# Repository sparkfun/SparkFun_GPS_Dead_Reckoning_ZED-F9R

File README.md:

SparkFun GPS-RTK Dead Reckoning Breakout - ZED-F9R, u.FL and SMA (Qwiic)
========================================

<table class="table table-hover table-striped table-bordered">
  <tr align="center">
   <td></td>
   <td></td>
  </tr>
  <tr align="center">
   <td><i>SparkFun GPS-RTK Dead Reckoning Breakout <br /> - ZED-F9R, u.FL (Qwiic) [<a href="https://www.sparkfun.com/products/22693">22693</a>]</i></td>
   <td><i>SparkFun GPS-RTK Dead Reckoning Breakout <br /> - ZED-F9R, SMA (Qwiic) [<a href="https://www.sparkfun.com/products/22660">GPS-22660</a>]</i></td>
  </tr>
</table>

The SparkFun GPS-RTK Dead Reckoning ZED-F9R Breakout (u.FL and SMA) is a high precision, sensor fusion GPS board with equally impressive configuration options and takes advantage of u-blox's Automotive Dead Reckoning (ADR) technology. The ZED-F9R module provides a highly accurate and continuous position by fusing a 3D IMU sensor, wheel ticks, a vehicle dynamics model, correction data, and GNSS measurements.

The ZED-F9R module is a 184-channel u-blox F9 engine GNSS receiver, meaning it can receive signals from the GPS, GLONASS, Galileo, and BeiDou constellations with ~0.2 meter accuracy! That's right, such accuracy can be achieved with an RTK navigation solution when used with a correction source. Note that the ZED-F9R can only operate as a rover, so you will need to connect to a base station. The module supports concurrent reception of four GNSS systems. The combination of GNSS and integrated 3D sensor measurements on the ZED-F9R provide accurate, real-time positioning rates of up to 30Hz.

Compared to other GPS modules, this breakout maximizes position accuracy in dense cities or covered areas. Even under poor signal conditions, continuous positioning is provided in urban environments and is also available during complete signal loss (e.g. short tunnels and parking garages). The ZED-F9R is the ultimate solution for autonomous robotic applications that require accurate positioning under challenging conditions.

Additionally, this u-blox receiver supports I2C (u-blox calls this Display Data Channel) which makes it perfect for the Qwiic compatibility so we don't have to use up our precious UART ports. Utilizing our handy Qwiic system, no soldering is required to connect it to the rest of your system. However, we still have broken out 0.1"-spaced pins in case you prefer to use a breadboard.

U-blox based GPS products are configurable using the popular, but dense, windows program called u-center. Plenty of different functions can be configured on the ZED-F9R: baud rates, update rates, geofencing, spoofing detection, external interrupts, SBAS/D-GPS, etc. All of this can be done within the SparkFun Arduino Library!

The SparkFun ZED-F9R GPS Breakout is also equipped with an on-board rechargeable battery that provides power to the RTC on the ZED-F9R. This reduces the time-to-first fix from a cold start (~24s) to a hot start (~2s). The battery will maintain RTC and GNSS orbit data without being connected to power for plenty of time.

Repository Contents
-------------------

* **/Documentation** - Data sheets, additional product information
* **/Hardware** - Eagle design files (.brd, .sch)
* **/Production** - Production panel files (.brd)

Documentation
--------------
* **[Library](https://github.com/sparkfun/SparkFun_u-blox_GNSS_v3)** - Arduino library v3 for the ZED-F9R.
    * _**Note**: We support two versions of the SparkFun u-blox GNSS library. [Version 2](https://github.com/sparkfun/SparkFun_u-blox_GNSS_Arduino_Library) and [Version 3](https://github.com/sparkfun/SparkFun_u-blox_GNSS_v3). Version 3 uses the u-blox Configuration Interface (VALSET and VALGET) to configure the module, instead of the deprecated UBX-CFG messages. For modules like the F9 and M10, we recommend upgrading to Version 3. However, older modules like the M8 do not support the Configuration Interface. For those you will need to keep using Version 2 of the library. We will continue to support both._
* **[Hookup Guide](https://learn.sparkfun.com/tutorials/1172)** - Basic hookup guide for the ZED-F9R.

Product Versions
----------------
* [GPS-22693](https://www.sparkfun.com/products/22693) - u.FL, v1.2
* [GPS-22660](https://www.sparkfun.com/products/22660) - SMA, V1.1
* [GPS-16344](https://www.sparkfun.com/products/16344) - u.FL, v1.0 initial release

Version History
---------------
* [v1.0](https://github.com/sparkfun/SparkFun_GPS_Dead_Reckoning_ZED-F9R/releases/tag/v1.0) - Initial Release

License Information
-------------------

This product is _**open source**_! 

Please review the LICENSE.md file for license information. 

If you have any questions or concerns on licensing, please contact technical support on our [SparkFun forums](https://forum.sparkfun.com/viewforum.php?f=152).

Distributed as-is; no warranty is given.

- Your friends at SparkFun.

_<COLLABORATION CREDIT>_

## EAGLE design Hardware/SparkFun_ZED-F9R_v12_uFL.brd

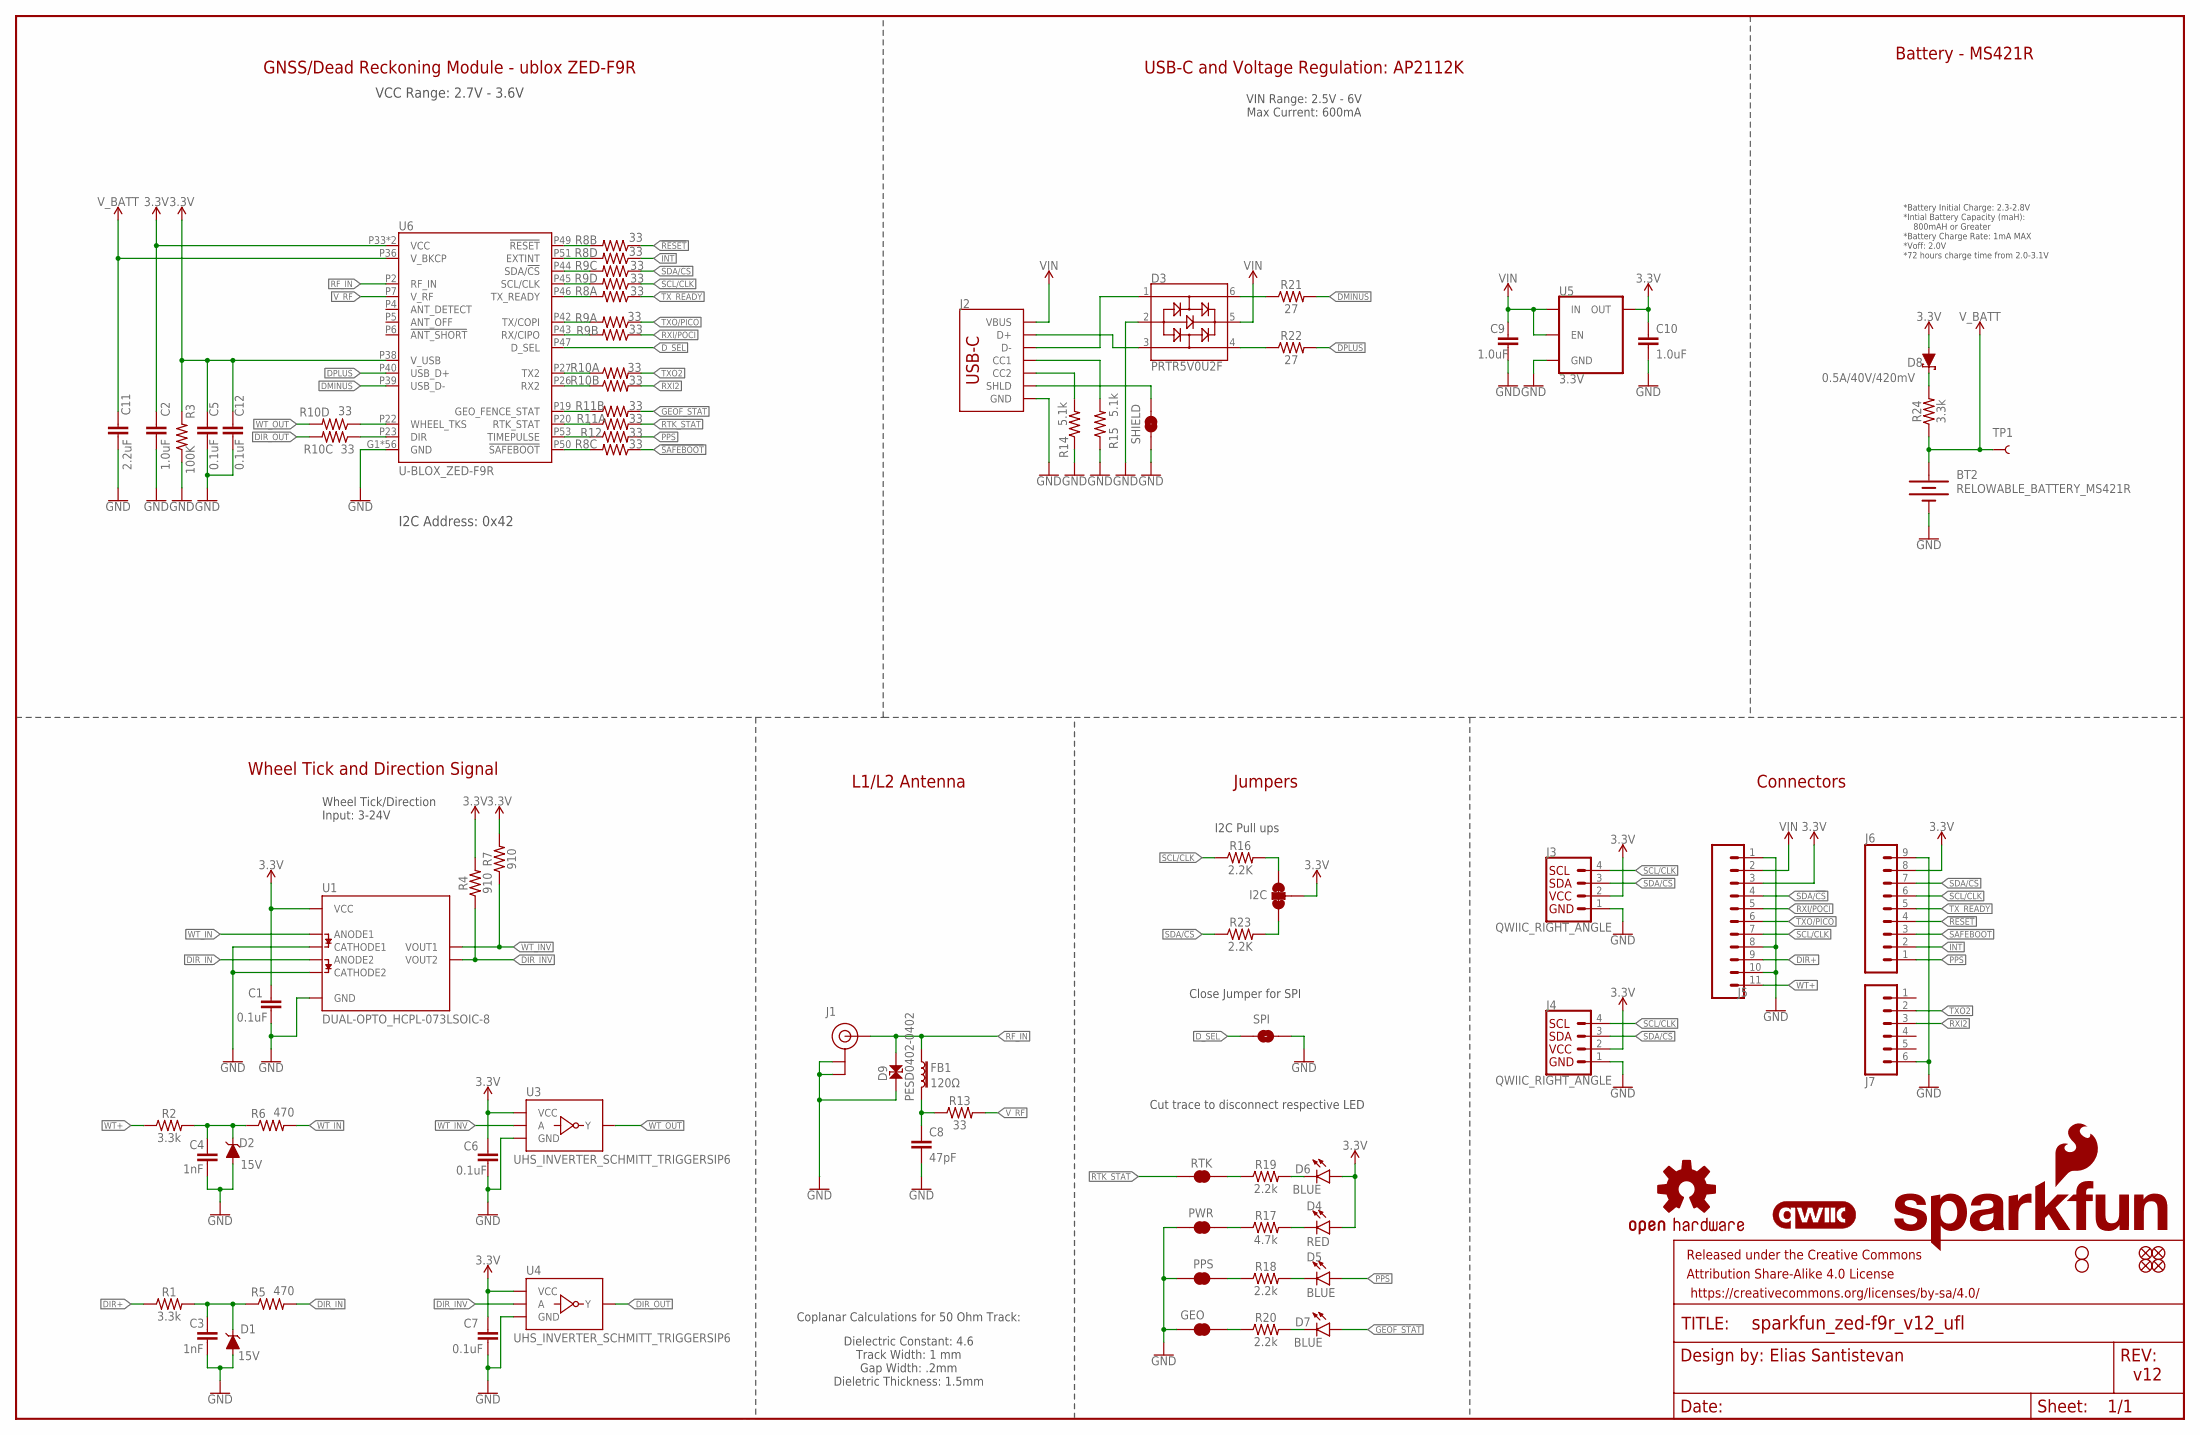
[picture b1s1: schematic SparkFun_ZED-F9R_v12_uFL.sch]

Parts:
$1_25_$_2020-03-30_22-52-05: STAND-OFFTIGHT; STAND-OFF-TIGHT
BT2: RELOWABLE_BATTERY_MS421R; MS421R_IV03E
C1, C5, C6, C7, C12: 0.1uF; 0402-TIGHT
C2, C9, C10: 1.0uF; 0402-TIGHT
C3, C4: 1nF; 0402
C8: 47pF; 0402
C11: 2.2uF; 0402-TIGHT
D1, D2: 15V; SOT23-3
D3: PRTR5V0U2F; SOT886
D4: RED; LED-0603
D5, D6, D7: BLUE; LED-0603
D8: 0.5A/40V/420mV; SOD-323
D9: PESD0402-0402; 0402
FB1: 120Ω; 0402
FD1, FD2, FD3, FD4: FIDUCIALUFIDUCIAL; FIDUCIAL-MICRO
FRAME1: FRAME-LEDGER; CREATIVE_COMMONS
GEO: JUMPER-SMT_2_NC_TRACE_SILK; SMT-JUMPER_2_NC_TRACE_SILK
H2: STAND-OFFTIGHT; STAND-OFF-TIGHT
I2C: JUMPER-SMT_3_2-NC_TRACE_SILK; SMT-JUMPER_3_2-NC_TRACE_SILK
J1: U.FL
J2: USB_C_2-LAYER_PADS; USB-C-16P-2LAYER-PADS
J3, J4: QWIIC_RIGHT_ANGLE; JST04_1MM_RA
J5: CONN_111X11_NO_SILK; 1X11_NO_SILK
J6: CONN_09NO_SILK; 1X09_NO_SILK
J7: CONN_06NO_SILK_NO_POP; 1X06_NO_SILK
LOGO1: OSHW-LOGOS; OSHW-LOGO-S
LOGO2: QWIIC_LOGO_4MM; QWIIC_4MM
LOGO3: SFE_LOGO_NAME_FLAME.2_INCH; SFE_LOGO_NAME_FLAME_.2
PPS: JUMPER-SMT_2_NC_TRACE_SILK; SMT-JUMPER_2_NC_TRACE_SILK
PWR: JUMPER-SMT_2_NC_TRACE_SILK; SMT-JUMPER_2_NC_TRACE_SILK
R1, R2, R24: 3.3k; 0603
R3: 100K; 0402
R4, R7: 910; 0603
R5, R6: 470; 0603
R8, R9, R10, R11: 33; 1206_RA
R12, R13: 33; 0603
R14, R15: 5.1k; 0402
R16, R23: 2.2K; 0402
R17: 4.7k; 0603
R18, R19, R20: 2.2k; 0603
R21, R22: 27; 0603
RTK: JUMPER-SMT_2_NC_TRACE_SILK; SMT-JUMPER_2_NC_TRACE_SILK
SHIELD: JUMPER-SMT_2_NC_TRACE_SILK; SMT-JUMPER_2_NC_TRACE_SILK
SPI: JUMPER-SMT_2_NO_SILK; SMT-JUMPER_2_NO_SILK
TP1: TEST-POINT3X5; PAD.03X.05
U1: DUAL-OPTO_HCPL-073LSOIC-8; SO08
U3, U4: UHS_INVERTER_SCHMITT_TRIGGERSIP6; SIP6_MICROPAK2
U5: 3.3V; SOT23-5
U6: U-BLOX_ZED-F9R; UBLOX_ZED_F9R

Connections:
3.3V: C1.1, C2.1, C5.1, C6.1, C7.1, C10.1, C12.1, D4.A, D6.A, D8.A, I2C.2, J3.2, J4.2, J5.3, J6.8, R3.2, R4.2, R7.2, U1.8 (VCC), U3.P6 (VCC), U4.P6 (VCC), U5.5 (OUT), U6.P33 (VCC), U6.P34 (VCC), U6.P38 (V_USB)
!RESET: J6.4, R8.P2 (1)
!SAFEBOOT: J6.3, R8.P3 (1)
DIR+: J5.9, R1.1
DIR_IN: R5.2, U1.4 (ANODE2)
DIR_INV: R4.1, U1.6 (VOUT2), U4.P2 (A)
DIR_OUT: R10.P6 (2), U4.P4 (Y)
DMINUS: R21.2, U6.P39 (USB_D-)
DPLUS: R22.2, U6.P40 (USB_D+)
D_SEL: SPI.1, U6.P47 (D_SEL)
GEOF_STAT: D7.A, R11.P7 (2)
GND: BT2.-, C1.2, C2.2, C3.2, C4.2, C5.2, C6.2, C7.2, C8.2, C9.2, C10.2, C11.2, C12.2, D1.1 (A), D2.1 (A), D3.2, D9.1, GEO.1, J1.1 (GND), J1.2 (GND), J2.GND, J2.GND2 (GND), J3.1, J4.1, J5.1, J5.8, J5.10, J6.9, J7.6, PPS.1, PWR.1, R3.1, R14.1, R15.1, SHIELD.1, SPI.2, U1.2 (CATHODE1), U1.3 (CATHODE2), U1.5 (GND), U3.P3 (GND), U4.P3 (GND), U5.2 (GND), U6.G1 (GND), U6.G2 (GND), U6.G3 (GND), U6.G4 (GND), U6.G5 (GND), U6.G6 (GND), U6.G7 (GND), U6.G8 (GND), U6.G9 (GND), U6.G10 (GND), U6.G11 (GND), U6.G12 (GND), U6.G13 (GND), U6.G14 (GND), U6.G15 (GND), U6.G16 (GND), U6.G17 (GND), U6.G18 (GND), U6.G19 (GND), U6.G20 (GND), U6.G21 (GND), U6.G22 (GND), U6.G23 (GND), U6.G24 (GND), U6.G25 (GND), U6.G26 (GND), U6.G27 (GND), U6.G28 (GND), U6.G29 (GND), U6.G30 (GND), U6.G31 (GND), U6.G32 (GND), U6.G33 (GND), U6.G34 (GND), U6.G35 (GND), U6.G36 (GND), U6.G37 (GND), U6.G38 (GND), U6.G39 (GND), U6.G40 (GND), U6.G41 (GND), U6.G42 (GND), U6.G43 (GND), U6.G44 (GND), U6.G45 (GND), U6.G46 (GND), U6.G47 (GND), U6.G48 (GND), U6.P1 (GND), U6.P3 (GND), U6.P12 (GND), U6.P14 (GND), U6.P32 (GND), U6.P37 (GND), U6.P41 (GND), U6.P48 (GND)
INT: J6.2, R8.P4 (1)
unnamed: I2C.1, R23.2
unnamed: D8.C, R24.2
unnamed: I2C.3, R16.2
unnamed: D4.C, R17.2
unnamed: C8.1, FB1.2, R13.1
unnamed: D3.3, J2.A6 (D+), J2.B6 (D+)
unnamed: D3.1, J2.A7 (D-), J2.B7 (D-)
unnamed: PWR.2, R17.1
unnamed: D3.6, R21.1
unnamed: D3.4, R22.1
unnamed: R8.P7 (2), U6.P49 (!RESET!)
unnamed: R8.P5 (2), U6.P51 (EXTINT)
unnamed: J2.B5 (CC2), R14.2
unnamed: J2.A5 (CC1), R15.2
unnamed: R9.P6 (2), U6.P44 (SDA/!CS!)
unnamed: R9.P5 (2), U6.P45 (SCL/CLK)
unnamed: R8.P8 (2), U6.P46 (TX_READY)
unnamed: R9.P8 (2), U6.P42 (TX/COPI)
unnamed: R9.P7 (2), U6.P43 (RX/CIPO)
unnamed: R10.P1 (1), U6.P27 (TX2)
unnamed: R19.1, RTK.2
unnamed: PPS.2, R18.1
unnamed: D5.C, R18.2
unnamed: D6.C, R19.2
unnamed: R10.P2 (1), U6.P26 (RX2)
unnamed: R11.P2 (1), U6.P19 (GEO_FENCE_STAT)
unnamed: R11.P1 (1), U6.P20 (RTK_STAT)
unnamed: R12.1, U6.P53 (TIMEPULSE)
unnamed: R8.P6 (2), U6.P50 (!SAFEBOOT!)
unnamed: R10.P4 (1), U6.P22 (WHEEL_TKS)
unnamed: R10.P3 (1), U6.P23 (DIR)
unnamed: GEO.2, R20.1
unnamed: D7.C, R20.2
unnamed: C4.1, D2.3 (C), R2.2, R6.1
unnamed: C3.1, D1.3 (C), R1.2, R5.1
PPS: D5.A, J6.1, R12.2
RF_IN: D9.2, FB1.1, J1.FEED (SIGNAL), U6.P2 (RF_IN)
RTK_STAT: R11.P8 (2), RTK.1
RXI2: J7.3, R10.P7 (2)
RXI/POCI: J5.5, R9.P2 (1)
SCL/CLK: J3.4, J4.4, J5.7, J6.6, R9.P4 (1), R16.1
SDA/!CS: J3.3, J4.3, J5.4, J6.7, R9.P3 (1), R23.1
SHIELD: J2.SHLD1 (SHLD), J2.SHLD2 (SHLD), J2.SHLD3 (SHLD), J2.SHLD4 (SHLD), SHIELD.2
TXO2: J7.2, R10.P8 (2)
TXO/PICO: J5.6, R9.P1 (1)
TX_READY: J6.5, R8.P1 (1)
VIN: C9.1, D3.5, J2.VBUS1 (VBUS), J2.VBUS2 (VBUS), J5.2, U5.1 (IN), U5.3 (EN)
V_BATT: BT2.+, C11.1, R24.1, TP1.1, U6.P36 (V_BKCP)
V_RF: R13.2, U6.P7 (V_RF)
WT+: J5.11, R2.1
WT_IN: R6.2, U1.1 (ANODE1)
WT_INV: R7.1, U1.7 (VOUT1), U3.P2 (A)
WT_OUT: R10.P5 (2), U3.P4 (Y)

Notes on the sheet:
v12
Elias Santistevan
GNSS/Dead Reckoning Module - ublox ZED-F9R
Battery - MS421R
Connectors
Jumpers
Close Jumper for SPI
I2C Pull ups
Cut trace to disconnect respective LED
L1/L2 Antenna
*Battery Initial Charge: 2.3-2.8V *Intial Battery Capacity (maH): 800mAH or Greater *Battery Charge Rate: 1mA MAX *Voff: 2.0V *72 hours charge time from 2.0-3.1V
VIN Range: 2.5V - 6V Max Current: 600mA
USB-C and Voltage Regulation: AP2112K
VCC Range: 2.7V - 3.6V
I2C Address: 0x42
Wheel Tick and Direction Signal
Wheel Tick/Direction Input: 3-24V
Coplanar Calculations for 50 Ohm Track:
Dielectric Constant: 4.6 Track Width: 1 mm Gap Width: .2mm Dieletric Thickness: 1.5mm

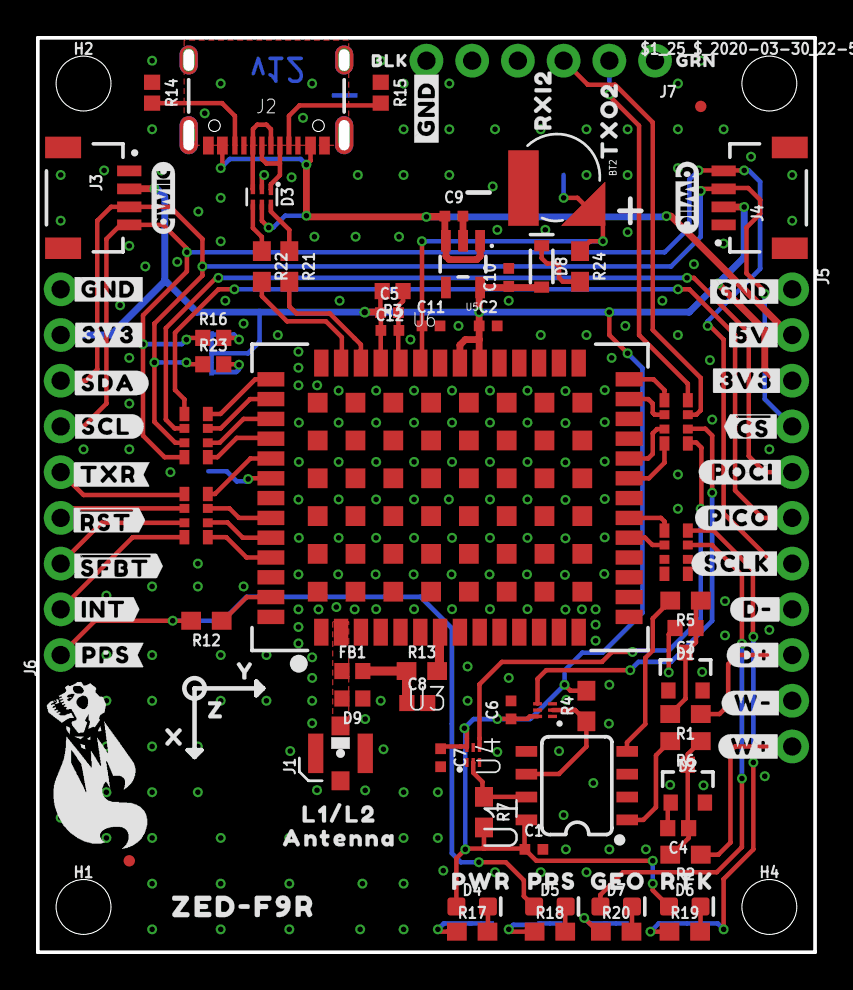
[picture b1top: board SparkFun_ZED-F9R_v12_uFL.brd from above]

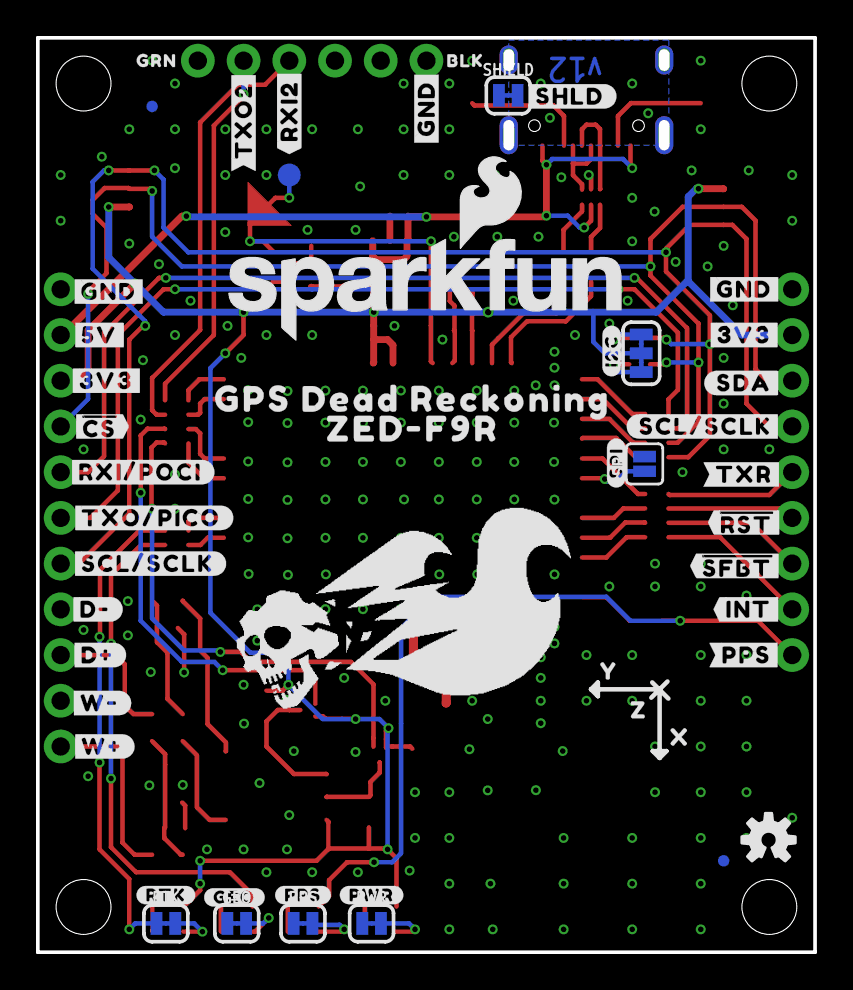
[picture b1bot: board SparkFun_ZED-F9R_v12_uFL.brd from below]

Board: 2 copper layers, 43.2 x 50.8 mm, 154 parts (50 on the bottom side), 66 nets.

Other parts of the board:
H1, H4: STAND-OFFTIGHT; STAND-OFF-TIGHT
LOGO4: QWIIC_LOGO_4MM; QWIIC_4MM
U$1: ZED#F9R21
U$2: L1#L26
U$3: ANTENNA6
U$4, U$32: X17
U$5, U$6, U$7, U$8, U$9, U$67: #GND#16
U$10: #D##241
U$11: #D##240
U$12: #W##244
U$13: #W##245
U$14, U$15, U$16, U$17: #3V3#17
U$18, U$21: #5V#17
U$19, U$20: DEAD#RECKONING#GPS#BOARD#SILK#FINAL#JPG
U$22: #SDA#235
U$23, U$71: BLK18
U$24: ##CS##25
U$26, U$70: GRN19
U$27: #SDA#236
U$28: #SCL#238
U$29: #TXR#248
U$30: ##RST##28
U$31: ##SFBT##26
U$33: #INT#1
U$34: #INT#0
U$35: #PPS#3
U$37: #SCLK#233
U$38: RXI229
U$39: PWR6
U$40: RTK12
U$41: GEO10
U$42: PPS8
U$43, U$44: Z19
U$45, U$49: Y18
U$46: #SCL#SCLK#2244
U$47: #GEO#12
U$48: #RTK#14
U$50: TXO2234
U$51: #PPS#10
U$52: ##CS##26
U$53: #SPI#4
U$54: #I2C#5
U$57: #SCL#SCLK#2243
U$58: #D##2249
U$59: #D##2248
U$60: #W##2253
U$61: #W##2252
U$62: #TXR#2255
U$63: ##RST##27
U$64: ##SFBT##29
U$65: #PPS#2
U$66: #PWR#8
U$68: #RXI2#34
U$69: #TXO2#235
U$72: GPS_DEAD_RECKONING24
U$73: ZED#F9R25
U$74: #SHLD#2258
U$75: #PICO#2
U$76: #POCI#3
U$77: #RXI#POCI#15
U$78: #TXO#PICO#16

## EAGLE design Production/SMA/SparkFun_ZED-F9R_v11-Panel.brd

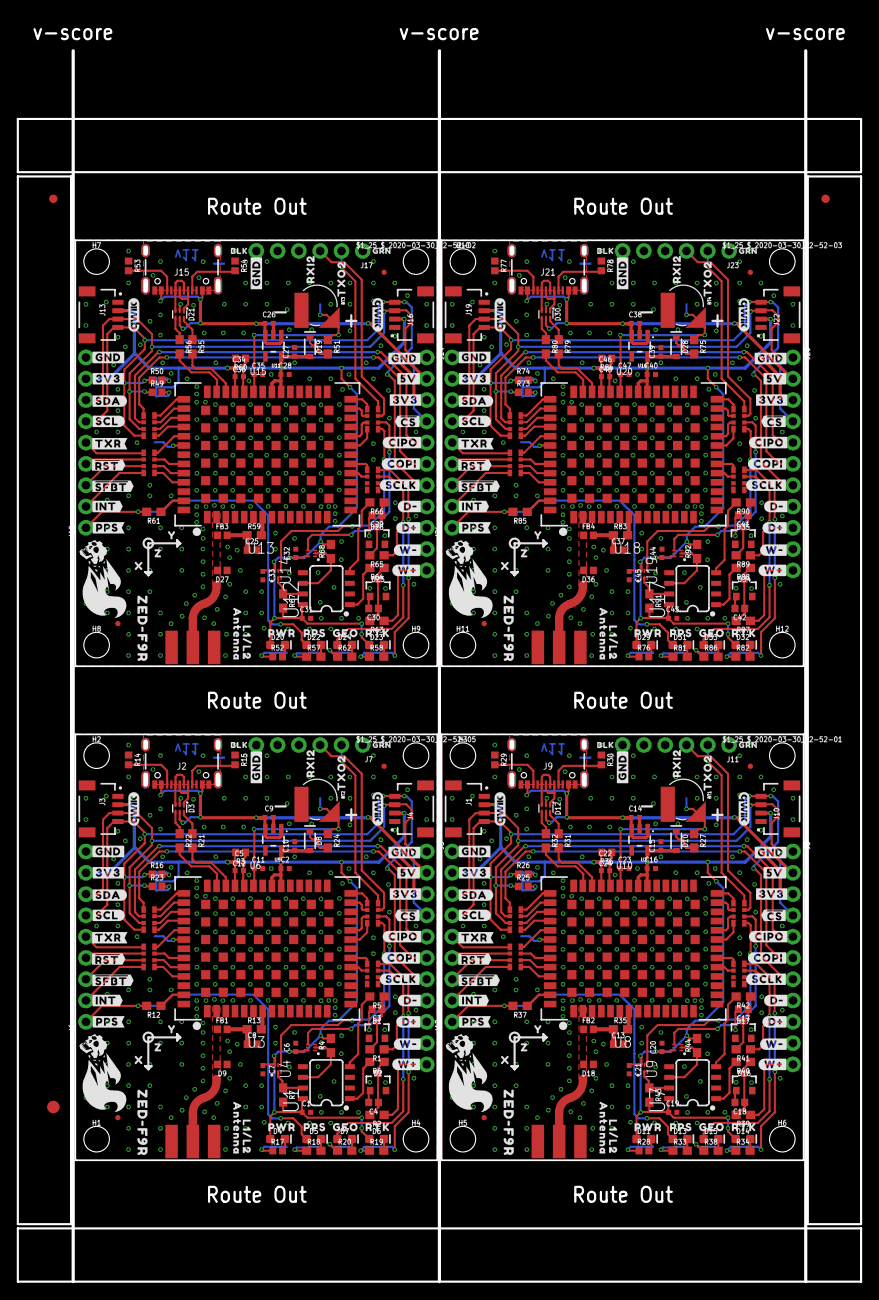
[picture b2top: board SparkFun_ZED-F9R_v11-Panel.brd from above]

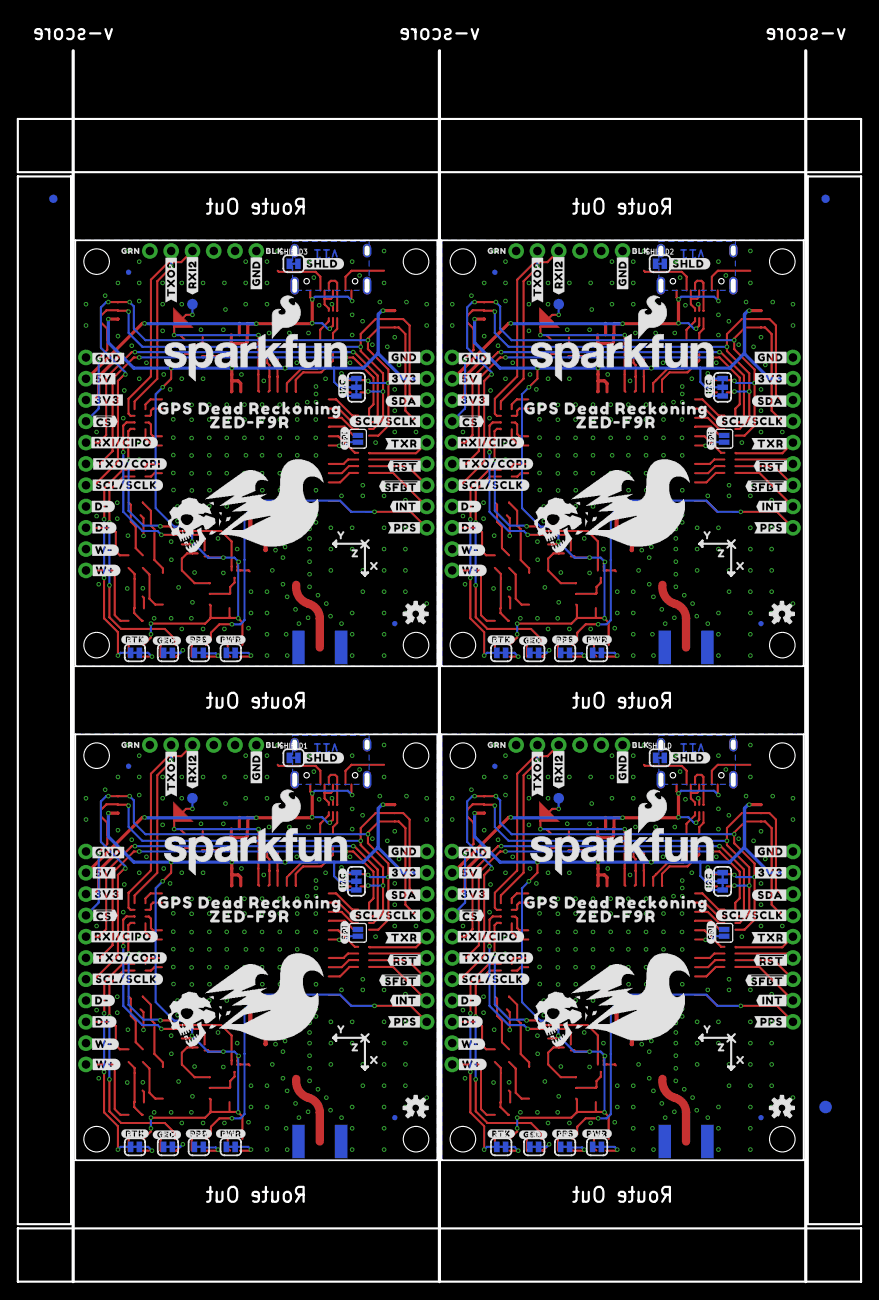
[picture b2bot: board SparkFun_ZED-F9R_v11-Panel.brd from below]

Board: 2 copper layers, 100.6 x 146.8 mm, 618 parts (203 on the bottom side), 264 nets.

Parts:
$1_25_$_2020-03-30_22-52-01, $1_25_$_2020-03-30_22-52-02, $1_25_$_2020-03-30_22-52-03, $1_25_$_2020-03-30_22-52-05: STAND-OFFTIGHT; STAND-OFF-TIGHT
BT1, BT2, BT3, BT4: RELOWABLE_BATTERY_MS421R; MS421R_IV03E
C1, C5, C6, C7, C12, C19, C20, C21, C22, C24, C31, C32, C33, C34, C36, C43, C44, C45, C46, C48: 0.1uF; 0402-TIGHT
C2, C9, C10, C14, C15, C16, C26, C27, C28, C38, C39, C40: 1.0uF; 0402-TIGHT
C3, C4, C17, C18, C29, C30, C41, C42: 1nF; 0402
C8, C13, C25, C37: 47pF; 0402
C11, C23, C35, C47: 2.2uF; 0402-TIGHT
D1, D2, D16, D17, D25, D26, D34, D35: 15V; SOT23-3
D3, D12, D21, D30: PRTR5V0U2F; SOT886
D4, D11, D20, D29: RED; LED-0603
D5, D6, D7, D13, D14, D15, D22, D23, D24, D31, D32, D33: BLUE; LED-0603
D8, D10, D19, D28: 0.5A/40V/420mV; SOD-323
D9, D18, D27, D36: PESD0402-0402; 0402
E1, E2, E3, E4: ANTENNA-SMA-GROUNDEDEDGE_SMA; SMA-EDGE
E$1, E$2, E$3, E$4: FIDUCIAL-1X2
E$5, E$6: FIDUCIAL-1.5X3
FB1, FB2, FB3, FB4: 120Ω; 0402
FD1, FD2, FD3, FD4, FD5, FD6, FD7, FD8, FD9, FD10, FD11, FD12, FD13, FD14, FD15, FD16: FIDUCIALUFIDUCIAL; FIDUCIAL-MICRO
GEO, GEO1, GEO2, GEO3: JUMPER-SMT_2_NC_TRACE_SILK; SMT-JUMPER_2_NC_TRACE_SILK
H1, H2, H3, H4, H5, H6, H7, H8, H9, H10, H11, H12: STAND-OFFTIGHT; STAND-OFF-TIGHT
I2C, I2C1, I2C2, I2C3: JUMPER-SMT_3_2-NC_TRACE_SILK; SMT-JUMPER_3_2-NC_TRACE_SILK
J1, J3, J4, J10, J13, J16, J19, J22: QWIIC_RIGHT_ANGLE; JST04_1MM_RA
J2, J9, J15, J21: USB-C-16P-2LAYER-PADS
J5, J8, J14, J20: 1X11_NO_SILK
J6, J12, J18, J24: 1X09_NO_SILK
J7, J11, J17, J23: 1X06_NO_SILK
LOGO1, LOGO7, LOGO11, LOGO15: OSHW-LOGOS; OSHW-LOGO-S
LOGO2, LOGO4, LOGO6, LOGO8, LOGO10, LOGO12, LOGO14, LOGO16: QWIIC_LOGO_4MM; QWIIC_4MM
LOGO3, LOGO5, LOGO9, LOGO13: SFE_LOGO_NAME_FLAME.2_INCH; SFE_LOGO_NAME_FLAME_.2
PPS, PPS1, PPS2, PPS3: JUMPER-SMT_2_NC_TRACE_SILK; SMT-JUMPER_2_NC_TRACE_SILK
PWR, PWR1, PWR2, PWR3: JUMPER-SMT_2_NC_TRACE_SILK; SMT-JUMPER_2_NC_TRACE_SILK
R1, R2, R24, R27, R39, R41, R51, R63, R65, R75, R87, R89: 3.3k; 0603
R3, R36, R60, R84: 100K; 0402
R4, R7, R43, R44, R67, R68, R91, R92: 910; 0603
R5, R6, R40, R42, R64, R66, R88, R90: 470; 0603
R8, R9, R10, R11, R45, R46, R47, R48, R69, R70, R71, R72, R93, R94, R95, R96: 33; 1206_RA
R12, R13, R35, R37, R59, R61, R83, R85: 33; 0603
R14, R15, R29, R30, R53, R54, R77, R78: 5.1k; 0402
R16, R23, R25, R26, R49, R50, R73, R74: 2.2K; 0402
R17, R28, R52, R76: 1KOHM-0402-1/16W-1%; 0402
R18, R19, R20, R33, R34, R38, R57, R58, R62, R81, R82, R86: 2.2k; 0603
R21, R22, R31, R32, R55, R56, R79, R80: 27; 0603
RTK, RTK1, RTK2, RTK3: JUMPER-SMT_2_NC_TRACE_SILK; SMT-JUMPER_2_NC_TRACE_SILK
SHIELD, SHIELD1, SHIELD2, SHIELD3: JUMPER-SMT_2_NC_TRACE_SILK; SMT-JUMPER_2_NC_TRACE_SILK
SPI, SPI1, SPI2, SPI3: JUMPER-SMT_2_NO_SILK; SMT-JUMPER_2_NO_SILK
TP1, TP2, TP3, TP4: TEST-POINT3X5; PAD.03X.05
U1, U7, U12, U17: DUAL-OPTO_HCPL-073LSOIC-8; SO08
U2, U5, U11, U16: 3.3V; SOT23-5
U3, U4, U8, U9, U13, U14, U18, U19: UHS_INVERTER_SCHMITT_TRIGGERSIP6; SIP6_MICROPAK2
U6, U10, U15, U20: U-BLOX_ZED-F9R; UBLOX_ZED_F9R
U$1, U$108, U$182, U$256: ZED#F9R21
U$2, U$109, U$183, U$257: L1#L26
U$3, U$110, U$184, U$258: ANTENNA6
U$4, U$32, U$111, U$112, U$185, U$186, U$259, U$260: X17
U$5, U$6, U$7, U$8, U$9, U$67, U$77, U$78, U$79, U$80, U$81, U$137, U$151, U$152, U$153, U$154, U$155, U$211, U$225, U$226, U$227, U$228, U$229, U$285: #GND#16
U$10, U$97, U$171, U$245: #D##241
U$11, U$98, U$172, U$246: #D##240
U$12, U$99, U$173, U$247: #W##244
U$13, U$100, U$174, U$248: #W##245
U$14, U$15, U$16, U$17, U$82, U$83, U$84, U$85, U$156, U$157, U$158, U$159, U$230, U$231, U$232, U$233: #3V3#17
U$18, U$21, U$86, U$87, U$160, U$161, U$234, U$235: #5V#17
U$19, U$20, U$75, U$76, U$149, U$150, U$223, U$224: DEAD#RECKONING#GPS#BOARD#SILK#FINAL#JPG
U$22, U$88, U$162, U$236: #SDA#235
U$23, U$71, U$102, U$141, U$176, U$215, U$250, U$289: BLK18
U$24, U$119, U$193, U$267: ##CS##25
U$25, U$94, U$168, U$242: #COPI#230
U$26, U$70, U$103, U$140, U$177, U$214, U$251, U$288: GRN19
U$27, U$89, U$163, U$237: #SDA#236
U$28, U$90, U$164, U$238: #SCL#238
U$29, U$91, U$165, U$239: #TXR#248
U$30, U$118, U$192, U$266: ##RST##28
U$31, U$92, U$166, U$240: ##SFBT##26
U$33, U$145, U$219, U$293: #INT#1
U$34, U$146, U$220, U$294: #INT#0
U$35, U$93, U$167, U$241: #PPS#3
U$36, U$95, U$169, U$243: #CIPO#232
U$37, U$96, U$170, U$244: #SCLK#233
U$38, U$101, U$175, U$249: RXI229
U$39, U$104, U$178, U$252: PWR6
U$40, U$105, U$179, U$253: RTK12
U$41, U$106, U$180, U$254: GEO10
U$42, U$107, U$181, U$255: PPS8
U$43, U$44, U$113, U$114, U$187, U$188, U$261, U$262: Z19
U$45, U$49, U$115, U$116, U$189, U$190, U$263, U$264: Y18
U$46, U$130, U$204, U$278: #SCL#SCLK#2244
U$47, U$131, U$205, U$279: #GEO#12
U$48, U$132, U$206, U$280: #RTK#14
U$50, U$117, U$191, U$265: TXO2234
U$51, U$133, U$207, U$281: #PPS#10
U$52, U$120, U$194, U$268: ##CS##26
U$53, U$136, U$210, U$284: #SPI#4
U$54, U$135, U$209, U$283: #I2C#5
U$55, U$147, U$221, U$295: #RXI#CIPO#32
U$56, U$148, U$222, U$296: #TXO#COPI#33
U$57, U$121, U$195, U$269: #SCL#SCLK#2243
U$58, U$122, U$196, U$270: #D##2249
U$59, U$123, U$197, U$271: #D##2248
U$60, U$124, U$198, U$272: #W##2253
U$61, U$125, U$199, U$273: #W##2252
U$62, U$126, U$200, U$274: #TXR#2255
U$63, U$127, U$201, U$275: ##RST##27
U$64, U$128, U$202, U$276: ##SFBT##29
U$65, U$129, U$203, U$277: #PPS#2
U$66, U$134, U$208, U$282: #PWR#8
U$68, U$138, U$212, U$286: #RXI2#34
U$69, U$139, U$213, U$287: #TXO2#235
U$72, U$142, U$216, U$290: GPS_DEAD_RECKONING24
U$73, U$143, U$217, U$291: ZED#F9R25
U$74, U$144, U$218, U$292: #SHLD#2258

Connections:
3.3V: C1.1, C2.1, C5.1, C6.1, C7.1, C10.1, C12.1, D4.A, D6.A, D8.A, I2C.2, J3.2, J4.2, J5.3, J6.8, R3.2, R4.2, R7.2, U1.8, U3.P6, U4.P6, U5.5, U6.P33, U6.P34, U6.P38
3.3V1: C15.1, C16.1, C19.1, C20.1, C21.1, C22.1, C24.1, D10.A, D11.A, D14.A, I2C1.2, J1.2, J8.3, J10.2, J12.8, R36.2, R43.2, R44.2, U2.5, U7.8, U8.P6, U9.P6, U10.P33, U10.P34, U10.P38
3.3V2: C27.1, C28.1, C31.1, C32.1, C33.1, C34.1, C36.1, D19.A, D20.A, D23.A, I2C2.2, J13.2, J14.3, J16.2, J18.8, R60.2, R67.2, R68.2, U11.5, U12.8, U13.P6, U14.P6, U15.P33, U15.P34, U15.P38
3.3V3: C39.1, C40.1, C43.1, C44.1, C45.1, C46.1, C48.1, D28.A, D29.A, D32.A, I2C3.2, J19.2, J20.3, J22.2, J24.8, R84.2, R91.2, R92.2, U16.5, U17.8, U18.P6, U19.P6, U20.P33, U20.P34, U20.P38
!RESET: J6.4, R8.P2
!RESET1: J12.4, R46.P2
!RESET2: J18.4, R70.P2
!RESET3: J24.4, R94.P2
!SAFEBOOT: J6.3, R8.P3
!SAFEBOOT1: J12.3, R46.P3
!SAFEBOOT2: J18.3, R70.P3
!SAFEBOOT3: J24.3, R94.P3
DIR+: J5.9, R1.1
DIR+1: J8.9, R41.1
DIR+2: J14.9, R65.1
DIR+3: J20.9, R89.1
DIR_IN: R5.2, U1.4
DIR_IN1: R42.2, U7.4
DIR_IN2: R66.2, U12.4
DIR_IN3: R90.2, U17.4
DIR_INV: R4.1, U1.6, U4.P2
DIR_INV1: R44.1, U7.6, U9.P2
DIR_INV2: R68.1, U12.6, U14.P2
DIR_INV3: R92.1, U17.6, U19.P2
DIR_OUT: R10.P6, U4.P4
DIR_OUT1: R47.P6, U9.P4
DIR_OUT2: R71.P6, U14.P4
DIR_OUT3: R95.P6, U19.P4
DMINUS: R21.2, U6.P39
DMINUS1: R31.2, U10.P39
DMINUS2: R55.2, U15.P39
DMINUS3: R79.2, U20.P39
DPLUS: R22.2, U6.P40
DPLUS1: R32.2, U10.P40
DPLUS2: R56.2, U15.P40
DPLUS3: R80.2, U20.P40
D_SEL: SPI.1, U6.P47
D_SEL1: SPI1.1, U10.P47
D_SEL2: SPI2.1, U15.P47
D_SEL3: SPI3.1, U20.P47
GEOF_STAT: D7.A, R11.P7
GEOF_STAT1: D15.A, R48.P7
GEOF_STAT2: D24.A, R72.P7
GEOF_STAT3: D33.A, R96.P7
GND: BT2.-, C1.2, C2.2, C3.2, C4.2, C5.2, C6.2, C7.2, C8.2, C9.2, C10.2, C11.2, C12.2, D1.1, D2.1, D3.2, D9.1, E1.GND@0, E1.GND@1, E1.GND@2, E1.GND@3, GEO.1, J2.GND, J2.GND2, J3.1, J4.1, J5.1, J5.8, J5.10, J6.9, J7.6, PPS.1, PWR.1, R3.1, R14.1, R15.1, SHIELD.1, SPI.2, U1.2, U1.3, U1.5, U3.P3, U4.P3, U5.2, U6.G1, U6.G2, U6.G3, U6.G4, U6.G5, U6.G6, U6.G7, U6.G8, U6.G9, U6.G10, U6.G11, U6.G12, U6.G13, U6.G14, U6.G15, U6.G16, U6.G17, U6.G18, U6.G19, U6.G20, U6.G21, U6.G22, U6.G23, U6.G24, U6.G25, U6.G26, U6.G27, U6.G28, U6.G29, U6.G30, U6.G31, U6.G32, U6.G33, U6.G34, U6.G35, U6.G36, U6.G37, U6.G38, U6.G39, U6.G40, U6.G41, U6.G42, U6.G43, U6.G44, U6.G45, U6.G46, U6.G47, U6.G48, U6.P1, U6.P3, U6.P12, U6.P14, U6.P32, U6.P37, U6.P41, U6.P48
GND1: BT1.-, C13.2, C14.2, C15.2, C16.2, C17.2, C18.2, C19.2, C20.2, C21.2, C22.2, C23.2, C24.2, D12.2, D16.1, D17.1, D18.1, E2.GND@0, E2.GND@1, E2.GND@2, E2.GND@3, GEO1.1, J1.1, J8.1, J8.8, J8.10, J9.GND, J9.GND2, J10.1, J11.6, J12.9, PPS1.1, PWR1.1, R29.1, R30.1, R36.1, SHIELD1.1, SPI1.2, U2.2, U7.2, U7.3, U7.5, U8.P3, U9.P3, U10.G1, U10.G2, U10.G3, U10.G4, U10.G5, U10.G6, U10.G7, U10.G8, U10.G9, U10.G10, U10.G11, U10.G12, U10.G13, U10.G14, U10.G15, U10.G16, U10.G17, U10.G18, U10.G19, U10.G20, U10.G21, U10.G22, U10.G23, U10.G24, U10.G25, U10.G26, U10.G27, U10.G28, U10.G29, U10.G30, U10.G31, U10.G32, U10.G33, U10.G34, U10.G35, U10.G36, U10.G37, U10.G38, U10.G39, U10.G40, U10.G41, U10.G42, U10.G43, U10.G44, U10.G45, U10.G46, U10.G47, U10.G48, U10.P1, U10.P3, U10.P12, U10.P14, U10.P32, U10.P37, U10.P41, U10.P48
GND2: BT3.-, C25.2, C26.2, C27.2, C28.2, C29.2, C30.2, C31.2, C32.2, C33.2, C34.2, C35.2, C36.2, D21.2, D25.1, D26.1, D27.1, E3.GND@0, E3.GND@1, E3.GND@2, E3.GND@3, GEO2.1, J13.1, J14.1, J14.8, J14.10, J15.GND, J15.GND2, J16.1, J17.6, J18.9, PPS2.1, PWR2.1, R53.1, R54.1, R60.1, SHIELD2.1, SPI2.2, U11.2, U12.2, U12.3, U12.5, U13.P3, U14.P3, U15.G1, U15.G2, U15.G3, U15.G4, U15.G5, U15.G6, U15.G7, U15.G8, U15.G9, U15.G10, U15.G11, U15.G12, U15.G13, U15.G14, U15.G15, U15.G16, U15.G17, U15.G18, U15.G19, U15.G20, U15.G21, U15.G22, U15.G23, U15.G24, U15.G25, U15.G26, U15.G27, U15.G28, U15.G29, U15.G30, U15.G31, U15.G32, U15.G33, U15.G34, U15.G35, U15.G36, U15.G37, U15.G38, U15.G39, U15.G40, U15.G41, U15.G42, U15.G43, U15.G44, U15.G45, U15.G46, U15.G47, U15.G48, U15.P1, U15.P3, U15.P12, U15.P14, U15.P32, U15.P37, U15.P41, U15.P48
GND3: BT4.-, C37.2, C38.2, C39.2, C40.2, C41.2, C42.2, C43.2, C44.2, C45.2, C46.2, C47.2, C48.2, D30.2, D34.1, D35.1, D36.1, E4.GND@0, E4.GND@1, E4.GND@2, E4.GND@3, GEO3.1, J19.1, J20.1, J20.8, J20.10, J21.GND, J21.GND2, J22.1, J23.6, J24.9, PPS3.1, PWR3.1, R77.1, R78.1, R84.1, SHIELD3.1, SPI3.2, U16.2, U17.2, U17.3, U17.5, U18.P3, U19.P3, U20.G1, U20.G2, U20.G3, U20.G4, U20.G5, U20.G6, U20.G7, U20.G8, U20.G9, U20.G10, U20.G11, U20.G12, U20.G13, U20.G14, U20.G15, U20.G16, U20.G17, U20.G18, U20.G19, U20.G20, U20.G21, U20.G22, U20.G23, U20.G24, U20.G25, U20.G26, U20.G27, U20.G28, U20.G29, U20.G30, U20.G31, U20.G32, U20.G33, U20.G34, U20.G35, U20.G36, U20.G37, U20.G38, U20.G39, U20.G40, U20.G41, U20.G42, U20.G43, U20.G44, U20.G45, U20.G46, U20.G47, U20.G48, U20.P1, U20.P3, U20.P12, U20.P14, U20.P32, U20.P37, U20.P41, U20.P48
INT: J6.2, R8.P4
INT1: J12.2, R46.P4
INT2: J18.2, R70.P4
INT3: J24.2, R94.P4
unnamed: I2C.1, R23.2
unnamed: D8.C, R24.2
unnamed: I2C.3, R16.2
unnamed: D4.C, R17.2
unnamed: C8.1, FB1.2, R13.1
unnamed: D3.3, J2.A6, J2.B6
unnamed: D3.1, J2.A7, J2.B7
unnamed: PWR.2, R17.1
unnamed: D3.6, R21.1
unnamed: D3.4, R22.1
unnamed: R8.P7, U6.P49
unnamed: R8.P5, U6.P51
unnamed: D10.C, R27.2
unnamed: J2.B5, R14.2
unnamed: J2.A5, R15.2
unnamed: R9.P6, U6.P44
unnamed: R9.P5, U6.P45
unnamed: R8.P8, U6.P46
unnamed: R9.P8, U6.P42
unnamed: R9.P7, U6.P43
unnamed: R10.P1, U6.P27
unnamed: R19.1, RTK.2
unnamed: PPS.2, R18.1
unnamed: D5.C, R18.2
unnamed: D6.C, R19.2
unnamed: R10.P2, U6.P26
unnamed: R11.P2, U6.P19
unnamed: R11.P1, U6.P20
unnamed: R12.1, U6.P53
unnamed: R8.P6, U6.P50
unnamed: R10.P4, U6.P22
unnamed: R10.P3, U6.P23
unnamed: GEO.2, R20.1
unnamed: D7.C, R20.2
unnamed: C4.1, D2.3, R2.2, R6.1
unnamed: I2C1.1, R25.2
unnamed: C3.1, D1.3, R1.2, R5.1
unnamed: I2C1.3, R26.2
unnamed: J9.B5, R29.2
unnamed: J9.A5, R30.2
unnamed: R34.1, RTK1.2
unnamed: PPS1.2, R33.1
unnamed: D13.C, R33.2
unnamed: D14.C, R34.2
unnamed: D11.C, R28.2
unnamed: PWR1.2, R28.1
unnamed: C13.1, FB2.2, R35.1
unnamed: D12.3, J9.A6, J9.B6
unnamed: D12.1, J9.A7, J9.B7
unnamed: D12.6, R31.1
unnamed: D12.4, R32.1
unnamed: R46.P7, U10.P49
unnamed: R46.P5, U10.P51
unnamed: R45.P6, U10.P44
unnamed: R45.P5, U10.P45
unnamed: R46.P8, U10.P46
unnamed: R45.P8, U10.P42
unnamed: R45.P7, U10.P43
unnamed: R47.P1, U10.P27
unnamed: R47.P2, U10.P26
unnamed: R48.P2, U10.P19
unnamed: R48.P1, U10.P20
unnamed: R37.1, U10.P53
unnamed: R46.P6, U10.P50
unnamed: R47.P4, U10.P22
unnamed: R47.P3, U10.P23
unnamed: GEO1.2, R38.1
unnamed: D15.C, R38.2
unnamed: C18.1, D16.3, R39.2, R40.1
unnamed: C17.1, D17.3, R41.2, R42.1
unnamed: D19.C, R51.2
unnamed: I2C2.1, R49.2
unnamed: I2C2.3, R50.2
unnamed: J15.B5, R53.2
unnamed: J15.A5, R54.2
unnamed: R58.1, RTK2.2
unnamed: PPS2.2, R57.1
unnamed: D22.C, R57.2
unnamed: D23.C, R58.2
unnamed: D20.C, R52.2
unnamed: PWR2.2, R52.1
unnamed: C25.1, FB3.2, R59.1
unnamed: D21.3, J15.A6, J15.B6
unnamed: D21.1, J15.A7, J15.B7
unnamed: D21.6, R55.1
unnamed: D21.4, R56.1
unnamed: R70.P7, U15.P49
unnamed: R70.P5, U15.P51
unnamed: R69.P6, U15.P44
unnamed: R69.P5, U15.P45
unnamed: R70.P8, U15.P46
unnamed: R69.P8, U15.P42
unnamed: R69.P7, U15.P43
unnamed: R71.P1, U15.P27
unnamed: R71.P2, U15.P26
unnamed: R72.P2, U15.P19
unnamed: R72.P1, U15.P20
unnamed: R61.1, U15.P53
unnamed: R70.P6, U15.P50
unnamed: R71.P4, U15.P22
unnamed: R71.P3, U15.P23
unnamed: GEO2.2, R62.1
unnamed: D24.C, R62.2
unnamed: C30.1, D25.3, R63.2, R64.1
unnamed: C29.1, D26.3, R65.2, R66.1
unnamed: D28.C, R75.2
unnamed: I2C3.1, R73.2
unnamed: I2C3.3, R74.2
unnamed: J21.B5, R77.2
unnamed: J21.A5, R78.2
unnamed: R82.1, RTK3.2
unnamed: PPS3.2, R81.1
unnamed: D31.C, R81.2
unnamed: D32.C, R82.2
unnamed: D29.C, R76.2
unnamed: PWR3.2, R76.1
unnamed: C37.1, FB4.2, R83.1
unnamed: D30.3, J21.A6, J21.B6
unnamed: D30.1, J21.A7, J21.B7
unnamed: D30.6, R79.1
unnamed: D30.4, R80.1
unnamed: R94.P7, U20.P49
unnamed: R94.P5, U20.P51
unnamed: R93.P6, U20.P44
unnamed: R93.P5, U20.P45
unnamed: R94.P8, U20.P46
unnamed: R93.P8, U20.P42
unnamed: R93.P7, U20.P43
unnamed: R95.P1, U20.P27
unnamed: R95.P2, U20.P26
unnamed: R96.P2, U20.P19
unnamed: R96.P1, U20.P20
unnamed: R85.1, U20.P53
unnamed: R94.P6, U20.P50
unnamed: R95.P4, U20.P22
unnamed: R95.P3, U20.P23
unnamed: GEO3.2, R86.1
unnamed: D33.C, R86.2
unnamed: C42.1, D34.3, R87.2, R88.1
unnamed: C41.1, D35.3, R89.2, R90.1
PPS: D5.A, J6.1, R12.2
PPS1: D13.A, J12.1, R37.2
PPS2: D22.A, J18.1, R61.2
PPS3: D31.A, J24.1, R85.2
RF_IN: D9.2, E1.SIG, FB1.1, U6.P2
RF_IN1: D18.2, E2.SIG, FB2.1, U10.P2
RF_IN2: D27.2, E3.SIG, FB3.1, U15.P2
RF_IN3: D36.2, E4.SIG, FB4.1, U20.P2
RTK_STAT: R11.P8, RTK.1
RTK_STAT1: R48.P8, RTK1.1
RTK_STAT2: R72.P8, RTK2.1
RTK_STAT3: R96.P8, RTK3.1
RXI1: J11.3, R47.P7
RXI2: J7.3, R10.P7
RXI3: J17.3, R71.P7
RXI4: J23.3, R95.P7
RXI/CIPO: J5.5, R9.P2
RXI/CIPO1: J8.5, R45.P2
RXI/CIPO2: J14.5, R69.P2
RXI/CIPO3: J20.5, R93.P2
SCL/CLK: J3.4, J4.4, J5.7, J6.6, R9.P4, R16.1
SCL/CLK1: J1.4, J8.7, J10.4, J12.6, R26.1, R45.P4
SCL/CLK2: J13.4, J14.7, J16.4, J18.6, R50.1, R69.P4
SCL/CLK3: J19.4, J20.7, J22.4, J24.6, R74.1, R93.P4
SDA/!CS: J3.3, J4.3, J5.4, J6.7, R9.P3, R23.1
SDA/!CS1: J1.3, J8.4, J10.3, J12.7, R25.1, R45.P3
SDA/!CS2: J13.3, J14.4, J16.3, J18.7, R49.1, R69.P3
SDA/!CS3: J19.3, J20.4, J22.3, J24.7, R73.1, R93.P3
SHIELD: J2.SHLD1, J2.SHLD2, J2.SHLD3, J2.SHLD4, SHIELD.2
SHIELD1: J9.SHLD1, J9.SHLD2, J9.SHLD3, J9.SHLD4, SHIELD1.2
SHIELD2: J15.SHLD1, J15.SHLD2, J15.SHLD3, J15.SHLD4, SHIELD2.2
SHIELD3: J21.SHLD1, J21.SHLD2, J21.SHLD3, J21.SHLD4, SHIELD3.2
TXO1: J11.2, R47.P8
TXO2: J7.2, R10.P8
TXO3: J17.2, R71.P8
TXO4: J23.2, R95.P8
TXO/COPI: J5.6, R9.P1
TXO/COPI1: J8.6, R45.P1
TXO/COPI2: J14.6, R69.P1
TXO/COPI3: J20.6, R93.P1
TX_READY: J6.5, R8.P1
TX_READY1: J12.5, R46.P1
TX_READY2: J18.5, R70.P1
TX_READY3: J24.5, R94.P1
VIN: C9.1, D3.5, J2.VBUS1, J2.VBUS2, J5.2, U5.1, U5.3
VIN1: C14.1, D12.5, J8.2, J9.VBUS1, J9.VBUS2, U2.1, U2.3
VIN2: C26.1, D21.5, J14.2, J15.VBUS1, J15.VBUS2, U11.1, U11.3
VIN3: C38.1, D30.5, J20.2, J21.VBUS1, J21.VBUS2, U16.1, U16.3
V_BATT: BT2.+, C11.1, R24.1, TP1.1, U6.P36
V_BATT1: BT1.+, C23.1, R27.1, TP2.1, U10.P36
V_BATT2: BT3.+, C35.1, R51.1, TP3.1, U15.P36
V_BATT3: BT4.+, C47.1, R75.1, TP4.1, U20.P36
V_RF: R13.2, U6.P7
V_RF1: R35.2, U10.P7
V_RF2: R59.2, U15.P7
V_RF3: R83.2, U20.P7
WT+: J5.11, R2.1
WT+1: J8.11, R39.1
WT+2: J14.11, R63.1
WT+3: J20.11, R87.1
WT_IN: R6.2, U1.1
WT_IN1: R40.2, U7.1
WT_IN2: R64.2, U12.1
WT_IN3: R88.2, U17.1
WT_INV: R7.1, U1.7, U3.P2
WT_INV1: R43.1, U7.7, U8.P2
WT_INV2: R67.1, U12.7, U13.P2
WT_INV3: R91.1, U17.7, U18.P2
WT_OUT: R10.P5, U3.P4
WT_OUT1: R47.P5, U8.P4
WT_OUT2: R71.P5, U13.P4
WT_OUT3: R95.P5, U18.P4

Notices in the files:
parts and their libraries:
SparkFun-Aesthetics: Licensing: Creative Commons ShareAlike 4.0 International - https://creativecommons.org/licenses/by-sa/4.0
SparkFun-Aesthetics: Released under the Creative Commons Attribution Share-Alike 4.0 License
SparkFun-Aesthetics: https://creativecommons.org/licenses/by-sa/4.0
